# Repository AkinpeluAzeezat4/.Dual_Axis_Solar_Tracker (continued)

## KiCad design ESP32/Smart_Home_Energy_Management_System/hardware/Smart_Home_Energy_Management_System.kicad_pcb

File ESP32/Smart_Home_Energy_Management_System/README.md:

# Smart Home Energy Management System

## Overview

This project is a modular Smart Home Energy Management System built around the ESP32-WROOM-32 using a structured PlatformIO architecture.

The system monitors the real electrical load using a PZEM-004T v3.0 energy meter and automatically manages household loads between the inverter supply and PHCN/Grid supply based on:

- Actual measured load power
- User-configured inverter power rating
- User-configured load margin percentage
- User-configured power value for each load
- PHCN/Grid availability
- Inverter availability

The system is designed to reduce inverter overload by intelligently selecting which loads should remain on inverter and which loads should be moved to PHCN/Grid when needed.

The device includes:

- ST7920 128x64 graphical LCD display
- Rotary encoder setup menu
- PCA9555 I/O expander for relay and source sensing
- PZEM-004T v3.0 energy monitoring
- Automatic source management
- Local Wi-Fi web dashboard
- Breathing heartbeat LED
- Non-blocking firmware design

---

# Features

- ESP32-WROOM-32 based controller
- PZEM-004T v3.0 live energy monitoring
- Voltage, current, power, and energy display
- Six-load energy management
- Inverter and PHCN/Grid source decision logic
- PCA9555 GPIO expander support
- ST7920 128x64 LCD user interface
- Rotary encoder menu navigation
- First-boot setup mode
- Runtime setup access using long encoder press
- Local web dashboard through ESP32 Access Point mode
- Configurable relay load power values
- Configurable inverter power rating
- Configurable load margin percentage
- Preferences-based setting storage
- Non-blocking firmware architecture
- Modular PlatformIO project structure

---

# Hardware Used

## Main Controller

- ESP32-WROOM-32 development board

## Display

- ST7920 128x64 graphical LCD

## Energy Monitoring

- PZEM-004T v3.0 AC energy monitoring module

## GPIO Expansion

- PCA9555 16-bit I/O expander

## User Input

- Rotary encoder with push button

## Output Devices

- Six relay-controlled load channels
- Source switching relay channels
- Heartbeat LED
- Indicator output from PCA9555

## Power Source Monitoring

- PHCN/Grid sense input
- Inverter sense input

---

# Pin Configuration

## ESP32-WROOM-32 Pin Assignment

| Function | GPIO |
|---|---|
| Heartbeat LED | GPIO2 |
| ST7920 LCD CS | GPIO5 |
| ST7920 LCD SCLK | GPIO18 |
| ST7920 LCD MOSI | GPIO23 |
| PCA9555 SDA | GPIO21 |
| PCA9555 SCL | GPIO22 |
| PZEM RX to ESP32 | GPIO16 |
| PZEM TX from ESP32 | GPIO17 |
| Encoder A / CLK | GPIO26 |
| Encoder B / DT | GPIO25 |
| Encoder SW | GPIO27 |

---

# ST7920 LCD Connection

| LCD Function | ESP32 GPIO |
|---|---|
| CS / RS | GPIO5 |
| SCLK / E | GPIO18 |
| MOSI / RW | GPIO23 |

The ST7920 must be placed in serial/SPI mode.

---

# PZEM-004T v3.0 Connection

| PZEM Function | ESP32 GPIO |
|---|---|
| PZEM TX | GPIO16 |
| PZEM RX | GPIO17 |

The PZEM is used as the actual power sensor for the system. The firmware uses the measured PZEM power value for energy-management decisions.

---

# PCA9555 Configuration

Default PCA9555 I2C address:

```text
0x20
```

## PCA9555 Pin Assignment

| PCA9555 Pin | Function |
|---|---|
| P00 | Load 1 source relay |
| P01 | Load 1 load relay |
| P02 | Load 2 source relay |
| P03 | Load 2 load relay |
| P04 | Load 3 source relay |
| P05 | Load 3 load relay |
| P06 | Load 4 source relay |
| P07 | Load 4 load relay |
| P10 | Load 5 source relay |
| P11 | Load 5 load relay |
| P12 | Load 6 source relay |
| P13 | Load 6 load relay |
| P14 | Indicator output |
| P15 | PHCN/Grid sense input |
| P16 | Inverter sense input |
| P17 | 12V enable output |

---

# Source Sense Logic

The firmware reads PHCN/Grid and inverter availability from the PCA9555 input pins.

The active logic is controlled in `Pins.cpp`:

```cpp
const bool SOURCE_SENSE_ACTIVE_HIGH = true;
const bool INVERTER_SENSE_ACTIVE_HIGH = true;
```

If the source-sensing circuit gives LOW when the source is available, change the values to:

```cpp
const bool SOURCE_SENSE_ACTIVE_HIGH = false;
const bool INVERTER_SENSE_ACTIVE_HIGH = false;
```

---

# Load Management Logic

The system does not depend on fixed assumed load values for its running decision.

It uses:

- Actual live power from the PZEM sensor
- User-saved inverter power rating
- User-saved load margin percentage
- User-saved load power value for each relay channel
- Real PHCN/Grid availability input
- Real inverter availability input

## Effective Inverter Limit

The effective inverter limit is calculated using:

```text
Effective Limit = Inverter Power Rating x Load Margin Percentage
```

Example:

```text
Inverter Rating = 5000 W
Load Margin = 90 %
Effective Limit = 4500 W
```

## Relay Source Meaning

```text
INVERTER = Load remains powered from inverter
PHCN     = Load is moved to grid/PHCN
```

When the load is within a safe range, the system keeps loads on inverter.

When the measured load approaches or exceeds the safe inverter limit and PHCN/Grid is available, the system selects which loads should remain on inverter and moves other loads to PHCN/Grid to protect the inverter.

If the inverter is unavailable, the system moves the loads away from inverter.

---

# LCD Operation Guide

The LCD shows two main runtime screens:

## Load Status Screen

This screen shows the source status of each load channel.

```text
INV = Load is on inverter
GRD = Load is on PHCN/Grid
```

## Consumption Screen

This screen shows live PZEM readings:

- Voltage
- Current
- Power
- Energy

The device alternates between the load status screen and the consumption screen during normal operation.

---

# Encoder Operation Guide

## First Boot Setup

If the device has not been configured before, it automatically enters setup mode.

## Boot Setup Entry

During startup, hold the encoder button within the boot window to enter setup mode.

```text
Boot window: 5 seconds
Required hold time: 3 seconds
```

## Runtime Setup Entry

During normal operation, hold the encoder button to enter setup mode.

```text
Required hold time: 5 seconds
```

## Menu Navigation

| Action | Function |
|---|---|
| Rotate encoder | Move through menu / change value |
| Press encoder | Select item / move to next setting |
| Long press encoder | Enter setup mode from runtime |

---

# Setup Menu

The setup menu contains:

- Relay Mode
- Timer Setup
- WiFi Config
- System Setup
- Exit

## Relay Mode

Relay Mode is used to set the configured power rating for each load channel.

The six load channels are configured one after another:

```text
Relay 1 Load Power
Relay 2 Load Power
Relay 3 Load Power
Relay 4 Load Power
Relay 5 Load Power
Relay 6 Load Power
```

The configured load values are saved to ESP32 Preferences memory.

## System Setup

System Setup is used to set:

- Inverter Power Rating
- Load Margin Percentage

The inverter power rating should match the real inverter capacity.

The load margin percentage defines how much of the inverter rating should be used before the system starts protecting the inverter.

## WiFi Config

WiFi Config displays the local server information.

Default Access Point:

```text
SSID: SHEMS-Controller
Password: *****
IP Address: 192.168.4.1
```

The password is masked in this README for GitHub publishing. The actual value can be changed in the local server module.

---

# Local Web Dashboard

The ESP32 creates a local Wi-Fi Access Point.

Connect a phone or laptop to the device Wi-Fi network, then open:

```text
http://192.168.4.1
```

The dashboard displays:

- Voltage
- Current
- Actual load power
- Energy
- PHCN/Grid status
- Inverter status
- Effective inverter limit
- Load-management decision
- Relay source status
- Relay configured load power values

The dashboard also allows updating the inverter rating, load margin, and relay load power values.

---

# Default Configuration

| Parameter | Default Value |
|---|---:|
| Relay 1 Load Power | 500 W |
| Relay 2 Load Power | 700 W |
| Relay 3 Load Power | 900 W |
| Relay 4 Load Power | 1200 W |
| Relay 5 Load Power | 1500 W |
| Relay 6 Load Power | 2000 W |
| Inverter Power Rating | 5000 W |
| Load Margin | 90 % |

These values can be changed from the LCD setup menu or the local web dashboard.

---

# Project Structure

```text
lib/
├── Actuators/
│   ├── load_relay/
│   └── source_relay/
├── Control/
│   ├── error_handling/
│   └── sleep_wake/
├── Display/
│   ├── lcd_screen/
│   └── led_indicator/
├── Drivers/
│   └── gpio_expander/
├── Input/
│   └── rotary_encoder/
├── Pins/
├── Power/
│   ├── inverter_sense/
│   ├── nepa_sense/
│   └── regulator/
├── Sensors/
│   └── pzem_sensor/
├── System/
│   ├── config_manager/
│   ├── load_manager/
│   ├── local_server/
│   ├── ndelay/
│   ├── reset/
│   └── shared_var/

src/
└── main.cpp
```

---

# PlatformIO Environment

```ini
[platformio]
default_envs = esp32dev

[env:esp32dev]
platform = espressif32@6.5.0
board = esp32dev
framework = arduino
monitor_speed = 115200
lib_deps =
    olikraus/U8g2@^2.36.17
    mandulaj/PZEM-004T-v30@^1.2.1
build_flags =
    -DARDUINO_USB_CDC_ON_BOOT=0
```

---

# Build and Upload

## Build

```bash
pio run
```

## Upload

```bash
pio run --target upload
```

## Serial Monitor

```bash
pio device monitor
```

---

# Operation Flow

1. Power on the system.
2. The ESP32 initializes the LCD, encoder, PCA9555, relays, PZEM, local server, and saved configuration.
3. If the system has not been configured before, setup mode opens automatically.
4. Configure relay load power values and inverter settings.
5. During runtime, the PZEM measures actual voltage, current, power, and energy.
6. The source-sense inputs report PHCN/Grid and inverter availability.
7. The load manager checks the actual load against the inverter safe limit.
8. If the load is safe, loads remain on inverter.
9. If the inverter is close to overload and PHCN/Grid is available, selected loads are moved to PHCN/Grid.
10. The LCD and web dashboard show the current system state.

---

# Important Notes

- The PZEM must be wired correctly because the system uses it for live load decisions.
- Do not use assumed sensor values during final deployment.
- Configure the actual inverter rating before testing the load-management behavior.
- Configure each relay load power according to the real appliance connected to that load channel.
- Confirm the PHCN/Grid and inverter sense logic before connecting real loads.
- Use properly rated relays, contactors, and wiring for AC load switching.
- Use isolation and proper protection when working with mains voltage.
- The firmware is designed to be non-blocking and should not use `delay()` in the main control flow.

---

# Safety Warning

This project involves AC mains power and inverter/grid source switching. All high-voltage wiring should be handled carefully and tested with proper isolation, fusing, earthing, and protection devices.

For real installation, use correctly rated relays or contactors and ensure there is no unsafe back-feed between inverter and PHCN/Grid sources.

---

# Future Improvements

- Real-time graphing on the local dashboard
- Manual override from the web dashboard
- Load priority setup from LCD
- OTA update support
- Cloud logging
- MQTT integration
- Mobile app integration
- SD card logging
- Historical energy report

---

# Author

Egbe Raymond

Electrical / Electronic Engineer  
Embedded Systems Developer  
Full Stack Developer

---

# License

This project is intended for educational, prototype, and development purposes.

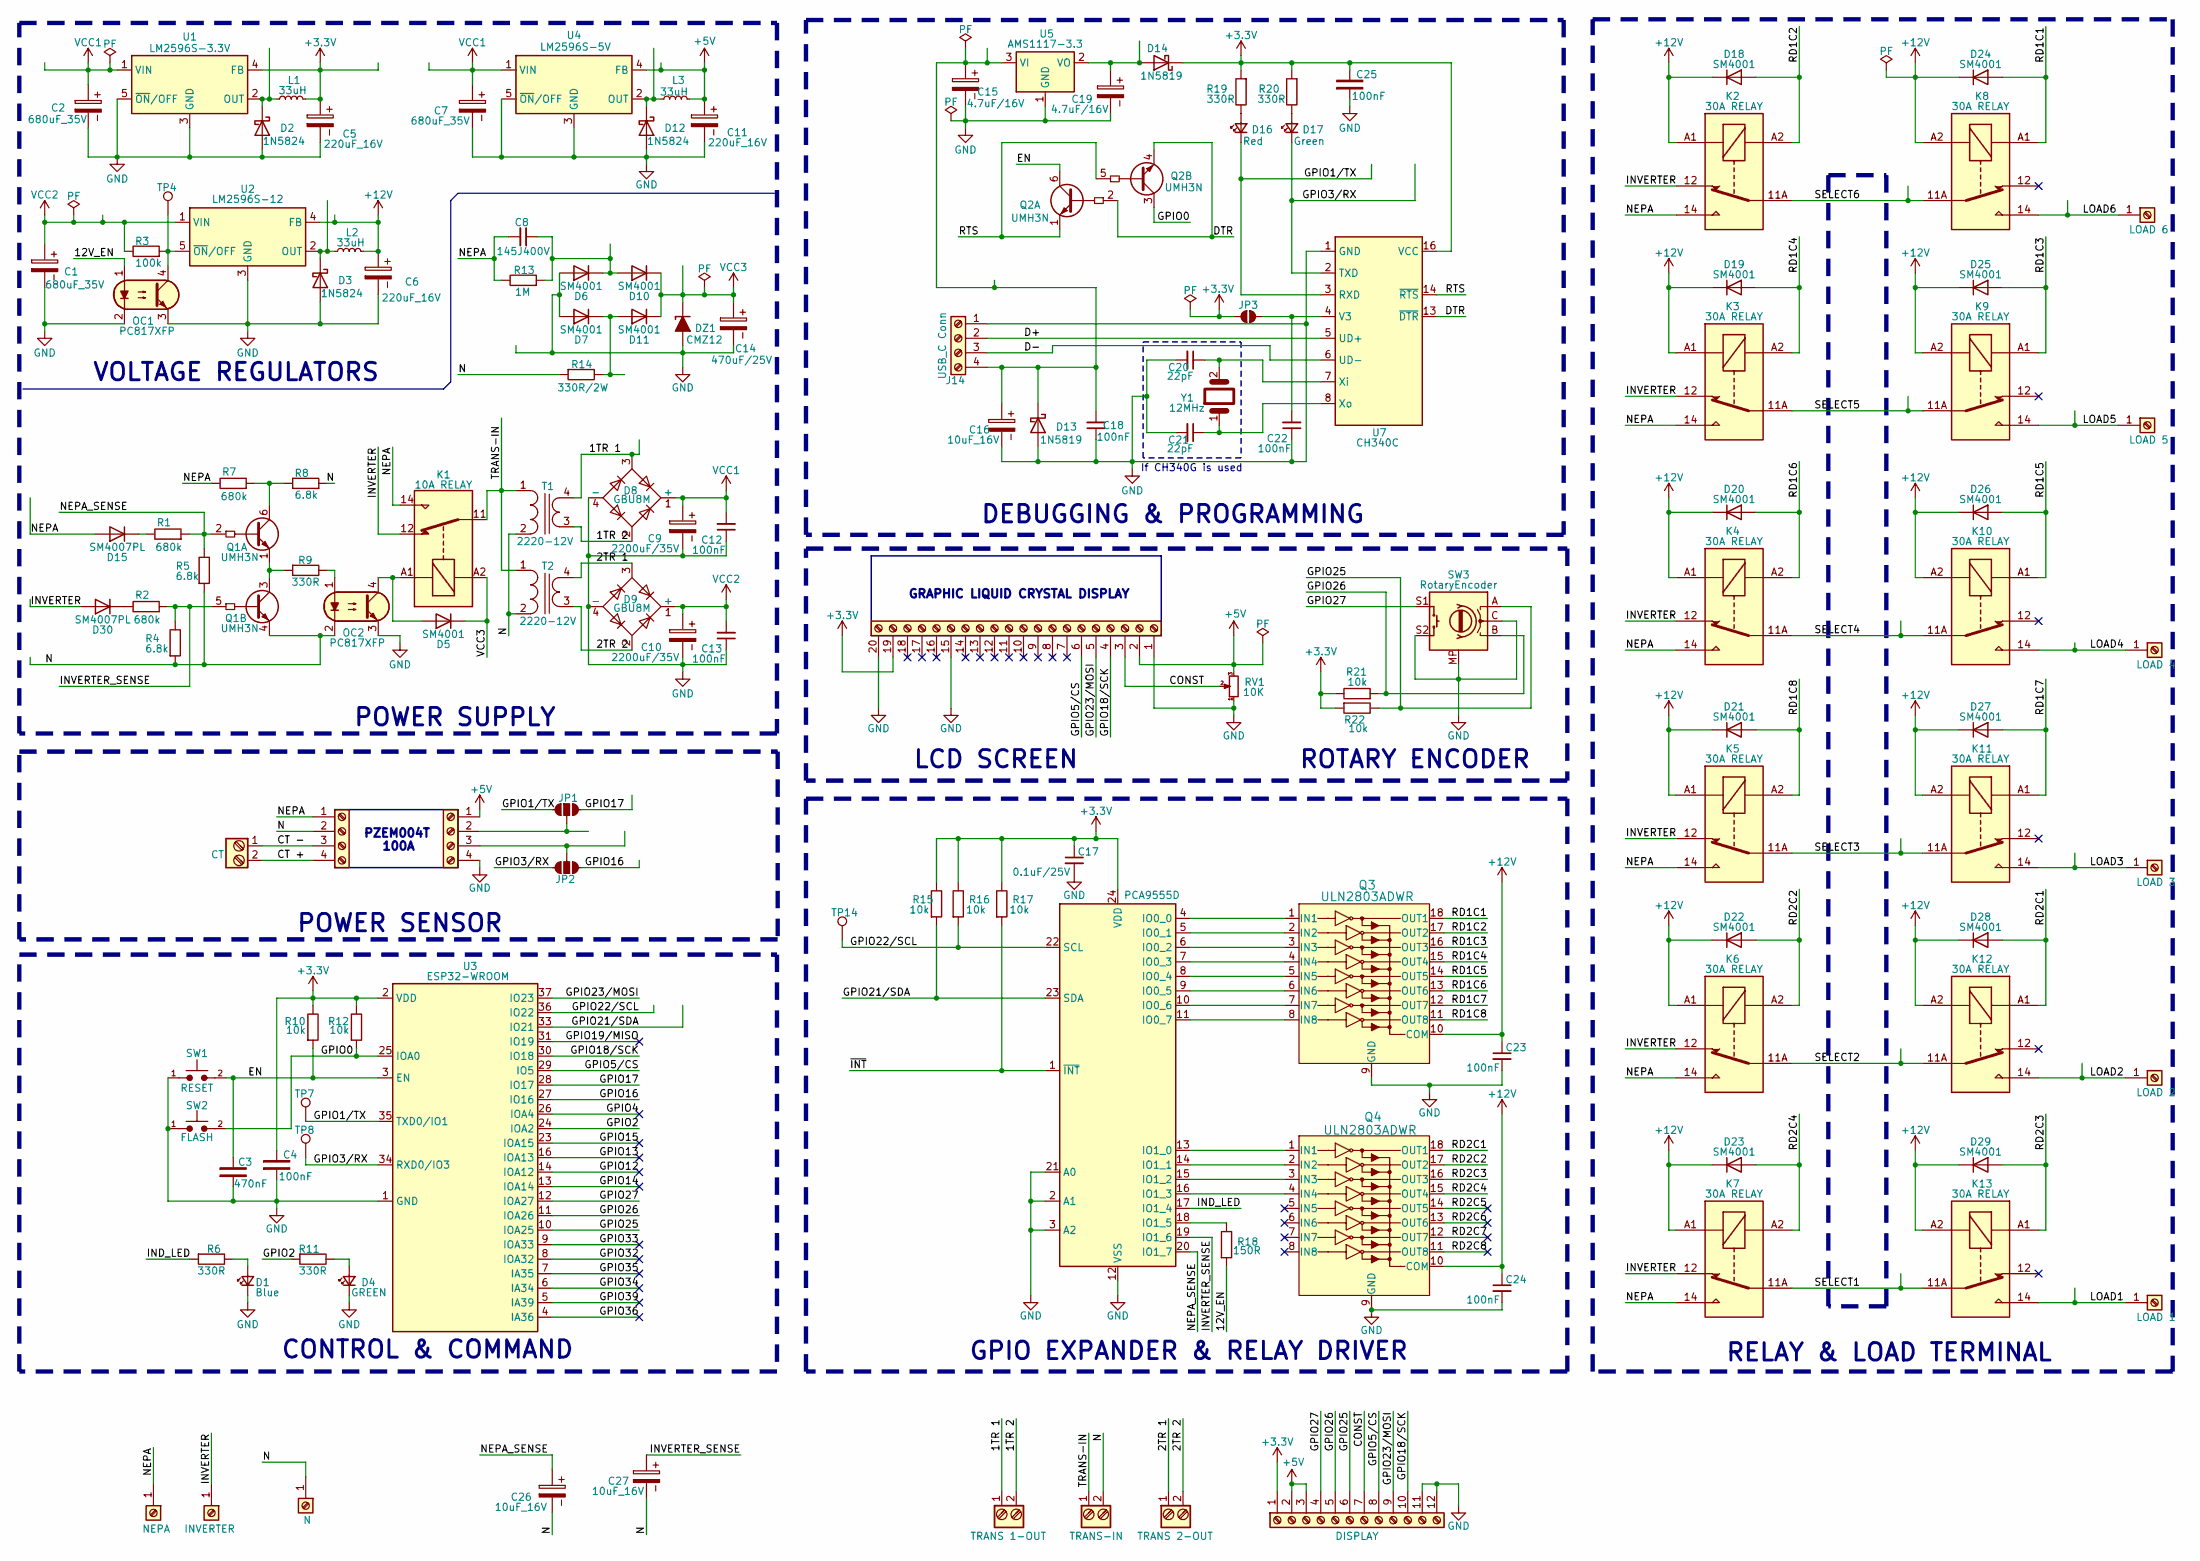
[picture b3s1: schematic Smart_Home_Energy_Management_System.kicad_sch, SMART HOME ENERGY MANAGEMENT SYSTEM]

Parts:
C1, C2, C7: 680uF_35V; CP_Elec_10x12.5
C3: 470nF; C_0805
C4, C12, C13, C18, C22, C25: 100nF; C_0805
C5, C6, C11: 220uF_16V; CP_Elec_6.3x7.7
C8: 145J400V; C_Rect_L19.0mm_W6.0mm_P15.00mm_MKS4
C9, C10: 2200uF/35V; CP_Radial_D18.0mm_P7.50mm
C14: 470uF/25V; CP_Elec_8x11.9
C15: 4.7uF/16V; C_CASE-B-3528-21(mm)
C16, C26, C27: 10uF_16V; C_CASE-B-3528-21(mm)
C17: 0.1uF/25V; C_0805; Voltage 25V; Tolerance 20%
C19: 4.7uF/16V; CP_EIA-3216-18_Kemet-A
C20, C21: 22pF; C_0805
C23, C24: 100nF; C_0805; Voltage 25V; Tolerance 20%
D1: Blue; LED_D3.0mm
D2, D3, D12: 1N5824; D_SMA
D4: GREEN; LED_D3.0mm
D5, D6, D7, D10, D11, D18, D19, D20, D21, D22, D23, D24, D25, D26, D27, D28, D29: SM4001; D_SMA
D8, D9: GBU8M; Diode_Bridge_Vishay_GBU
D13, D14: 1N5819; D_SMA
D15, D30: SM4007PL; D_SMA
D16: Red; LED_D3.0mm
D17: Green; LED_D3.0mm
DZ1: CMZ12; D_SOD-123
J1: NEPA; TestPoint_Plated_Hole_D5.0mm
J2: INVERTER; TestPoint_Plated_Hole_D5.0mm
J3: CT; PinHeader_1x02_P2.54mm_Vertical
J6: PZEM_LOAD; TerminalBlock_MaiXu_MX126-5.0-04P_1x04_P5.00mm
J10: N; TestPoint_Plated_Hole_D5.0mm
J11: PZEM_SIG; PinHeader_1x04_P2.54mm_Vertical
J14: USB_C Conn; PinHeader_1x04_P2.54mm_Vertical
J15: TRANS 1-OUT; TerminalBlock_Phoenix_PT-1,5-2-5.0-H_1x02_P5.00mm_Horizontal
J16: 128X64 GLCD
J17: TRANS-IN; TerminalBlock_Phoenix_PT-1,5-2-5.0-H_1x02_P5.00mm_Horizontal
J18: TRANS 2-OUT; TerminalBlock_Phoenix_PT-1,5-2-5.0-H_1x02_P5.00mm_Horizontal
J19: DISPLAY; PinHeader_1x12_P2.54mm_Vertical
J20: LOAD 6; TestPoint_Plated_Hole_D5.0mm
J21: LOAD 5; TestPoint_Plated_Hole_D5.0mm
J22: LOAD 4; TestPoint_Plated_Hole_D5.0mm
J23: LOAD 3; TestPoint_Plated_Hole_D5.0mm
J24: LOAD 2; TestPoint_Plated_Hole_D5.0mm
J25: LOAD 1; TestPoint_Plated_Hole_D5.0mm
JP1, JP2: SolderJumper-3_P1.3mm_Open_Pad1.0x1.5mm
JP3: SolderJumper-2_P1.3mm_Open_Pad1.0x1.5mm
K1: 10A RELAY; Relay_SPDT_Finder_36.11
K2, K3, K4, K5, K6, K7, K8, K9, K10, K11, K12, K13: 30A RELAY; Relay_SPDT_RAYEX-L90
L1, L2, L3: 33uH; L_12x12mm_H6mm
OC1, OC2: PC817XFP; SOP-4_4.4x2.6mm_P1.27mm
Q1, Q2: UMH3N; SOT-363_SC-70-6
Q3, Q4: ULN2803ADWR; SOIC-18_W7.5mm; MPN ULN2803ADWR; Digi-Key_PN 296-15777-1-ND
R1, R2, R7: 680k; R_0805
R3: 100k; R_0805
R4, R5, R8: 6.8k; R_0805
R6, R9, R11, R19, R20: 330R; R_0805
R10, R12, R15, R16, R17, R21, R22: 10k; R_0805
R13: 1M; R_Axial_DIN0207_L6.3mm_D2.5mm_P7.62mm_Horizontal
R14: 330R/2W; R_Axial_DIN0309_L9.0mm_D3.2mm_P20.32mm_Horizontal
R18: 150R; R_0805
RV1: 10K; Potentiometer_Bourns_3296W_Vertical
SW1: RESET; SW_TS-1088-AR02016
SW2: FLASH; SW_TS-1088-AR02016
SW3: RotaryEncoder
T1, T2: 2220-12V
TP4, TP7, TP8, TP14: TestPoint; TestPoint_Pad_D1.5mm
U1: LM2596S-3.3V; TO-263-5_L10.2-W8.9-P1.70-TL
U2: LM2596S-12; TO-263-5_L10.2-W8.9-P1.70-TL
U3: ESP32-WROOM; ESP32-WROOM-32E
U4: LM2596S-5V; TO-263-5_L10.2-W8.9-P1.70-TL
U5: AMS1117-3.3; SOT-223-3_L6.5-W3.4-P2.30-LS7.0-BR
U6: PCA9555D; SOIC-24W_7.5x15.4mm_P1.27mm
U7: CH340C; SOIC-16_3.9x9.9mm_P1.27mm
Y1: 12MHz; CRYSTAL-SMD_L11.5-W4.8-LS12.7

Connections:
+3.3V: C4.2, C5.1, C17.1, C25.2, D14.1 (K), J16.19, J19.1, JP3.2 (B), L1.2, R10.2, R12.2, R15.2, R16.2, R17.2, R19.1, R20.1, R21.2, R22.1, U1.4 (FB), U3.2 (VDD), U6.24 (VDD), U7.16 (VCC)
+5V: C11.1, J11.1, J16.2, J19.2, J19.3, L3.2, RV1.3, U4.4 (FB)
+12V: C6.1, C23.1, C24.1, D18.1 (K), D19.1 (K), D20.1 (K), D21.1 (K), D22.1 (K), D23.1 (K), D24.1 (K), D25.1 (K), D26.1 (K), D27.1 (K), D28.1 (K), D29.1 (K), K2.A1, K3.A1, K4.A1, K5.A1, K6.A1, K7.A1, K8.A2, K9.A2, K10.A2, K11.A2, K12.A2, K13.A2, L2.2, Q3.10 (COM), Q4.10 (COM), U2.4 (FB)
/1TR 1: D8.3, J15.1, T1.4 (SB)
/1TR 2: D8.2, J15.2, T1.3 (SA)
/2TR 1: D9.3, J18.1, T2.4 (SB)
/2TR 2: D9.2, J18.2, T2.3 (SA)
/12V_EN: OC1.1, R18.1
/CONST: J16.3, J19.7, RV1.2
/CT +: J3.2, J6.4
/CT -: J3.1, J6.3
/D+: J14.2, U7.5 (UD+)
/D-: J14.3, U7.6 (UD-)
/DTR: Q2.2 (B1), Q2.4 (E2), U7.13 (~DTR)
/EN: C3.2, Q2.6 (C1), R10.1, SW1.2, U3.3 (EN)
/GPIO0: Q2.3 (C2), R12.1, SW2.2, U3.25 (IOA0)
/GPIO1/TX: D16.1 (K), JP1.1 (A), TP7.1, U3.35 (TXD0/IO1), U7.3 (RXD)
/GPIO2: R11.1, U3.24 (IOA2)
/GPIO3/RX: D17.1 (K), JP2.3 (C), TP8.1, U3.34 (RXD0/IO3), U7.2 (TXD)
/GPIO4: U3.26 (IOA4)
/GPIO5/CS: J16.6, J19.8, U3.29 (IO5)
/GPIO12: U3.14 (IOA12)
/GPIO13: U3.16 (IOA13)
/GPIO14: U3.13 (IOA14)
/GPIO15: U3.23 (IOA15)
/GPIO16: JP2.1 (A), U3.27 (IO16)
/GPIO17: JP1.3 (C), U3.28 (IO17)
/GPIO18/SCK: J16.4, J19.10, U3.30 (IO18)
/GPIO19/MISO: U3.31 (IO19)
/GPIO21/SDA: R15.1, U3.33 (IO21), U6.23 (SDA)
/GPIO22/SCL: R16.1, TP14.1, U3.36 (IO22), U6.22 (SCL)
/GPIO23/MOSI: J16.5, J19.9, U3.37 (IO23)
/GPIO25: J19.6, R22.2, SW3.A, U3.10 (IOA25)
/GPIO26: J19.5, R21.1, SW3.B, U3.11 (IOA26)
/GPIO27: J19.4, SW3.S1, U3.12 (IOA27)
/GPIO32: U3.8 (IOA32)
/GPIO33: U3.9 (IOA33)
/GPIO34: U3.6 (IA34)
/GPIO35: U3.7 (IA35)
/GPIO36: U3.4 (IA36)
/GPIO39: U3.5 (IA39)
/IND_LED: R6.1, U6.17 (IO1_4)
/INVERTER: D30.2 (A), J2.1, K1.12, K2.12, K3.12, K4.12, K5.12, K6.12, K7.12
/INVERTER_SENSE: C27.1, Q1.5 (B2), R2.1, R4.2, U6.19 (IO1_6)
/LOAD1: J25.1, K13.14
/LOAD2: J24.1, K12.14
/LOAD3: J23.1, K11.14
/LOAD4: J22.1, K10.14
/LOAD5: J21.1, K9.14
/LOAD6: J20.1, K8.14
/N: C26.2, C27.2, J6.2, J10.1, J17.2, OC2.2, Q1.4 (E2), R4.1, R5.1, R8.1, R14.1, T1.2 (AB), T2.2 (AB)
/NEPA: C8.2, D15.2 (A), J1.1, J6.1, K1.14, K2.14, K3.14, K4.14, K5.14, K6.14, K7.14, R7.2, R13.2
/NEPA_SENSE: C26.1, Q1.2 (B1), R1.1, R5.2, U6.20 (IO1_7)
/RD1C1: D24.2 (A), K8.A1, Q3.18 (OUT1)
/RD1C2: D18.2 (A), K2.A2, Q3.17 (OUT2)
/RD1C3: D25.2 (A), K9.A1, Q3.16 (OUT3)
/RD1C4: D19.2 (A), K3.A2, Q3.15 (OUT4)
/RD1C5: D26.2 (A), K10.A1, Q3.14 (OUT5)
/RD1C6: D20.2 (A), K4.A2, Q3.13 (OUT6)
/RD1C7: D27.2 (A), K11.A1, Q3.12 (OUT7)
/RD1C8: D21.2 (A), K5.A2, Q3.11 (OUT8)
/RD2C1: D28.2 (A), K12.A1, Q4.18 (OUT1)
/RD2C2: D22.2 (A), K6.A2, Q4.17 (OUT2)
/RD2C3: D29.2 (A), K13.A1, Q4.16 (OUT3)
/RD2C4: D23.2 (A), K7.A2, Q4.15 (OUT4)
/RD2C5: Q4.14 (OUT5)
/RD2C6: Q4.13 (OUT6)
/RD2C7: Q4.12 (OUT7)
/RD2C8: Q4.11 (OUT8)
/RTS: Q2.1 (E1), Q2.5 (B2), U7.14 (~RTS)
/SELECT1: K7.11A, K7.11B, K13.11A, K13.11B
/SELECT2: K6.11A, K6.11B, K12.11A, K12.11B
/SELECT3: K5.11A, K5.11B, K11.11A, K11.11B
/SELECT4: K4.11A, K4.11B, K10.11A, K10.11B
/SELECT5: K3.11A, K3.11B, K9.11A, K9.11B
/SELECT6: K2.11A, K2.11B, K8.11A, K8.11B
/TRANS-IN: J17.1, K1.11, T1.1 (AA), T2.1 (AA)
/~INT: R17.1, U6.1 (~INT)
GND: C1.2, C2.2, C3.1, C4.1, C5.2, C6.2, C7.2, C9.2, C10.2, C11.2, C12.1, C13.1, C14.2, C15.2, C16.2, C17.2, C18.1, C19.2, C20.2, C21.2, C22.1, C23.2, C24.2, C25.1, D1.1 (K), D2.2 (A), D3.2 (A), D4.1 (K), D6.2 (A), D7.2 (A), D8.4 (-), D9.4 (-), D12.2 (A), D13.2 (A), DZ1.2 (A), J11.4, J14.1, J16.1, J16.15, J16.20, J19.11, J19.12, OC1.2, OC1.3, OC2.3, Q3.9 (GND), Q4.9 (GND), RV1.1, SW1.1, SW2.1, SW3.C, SW3.MP, SW3.S2, U1.3 (GND), U1.5 (~ON/OFF), U1.6 (GND), U2.3 (GND), U2.6 (GND), U3.1 (GND), U3.15 (GND), U3.38 (GND), U3.39 (GND), U4.3 (GND), U4.5 (~ON/OFF), U4.6 (GND), U5.1 (GND), U6.2 (A1), U6.3 (A2), U6.12 (VSS), U6.21 (A0), U7.1 (GND)
unnamed: D1.2 (A), R6.2
unnamed: D2.1 (K), L1.1, U1.2 (OUT)
unnamed: D3.1 (K), L2.1, U2.2 (OUT)
unnamed: D4.2 (A), R11.2
unnamed: D5.2 (A), K1.A1, OC2.4
unnamed: C8.1, D6.1 (K), D10.2 (A), R13.1
unnamed: D7.1 (K), D11.2 (A), R14.2
unnamed: D12.1 (K), L3.1, U4.2 (OUT)
unnamed: C15.1, C16.1, C18.2, D13.1 (K), J14.4, U5.3 (VI)
unnamed: C19.1, D14.2 (A), U5.2 (VO), U5.4 (VO)
unnamed: D15.1 (K), R1.2
unnamed: D16.2 (A), R19.2
unnamed: D17.2 (A), R20.2
unnamed: D30.1 (K), R2.2
unnamed: J11.2, JP1.2 (B)
unnamed: J11.3, JP2.2 (B)
unnamed: C22.2, JP3.1 (A), U7.4 (V3)
unnamed: OC2.1, R9.2
unnamed: Q1.6 (C1), R7.1, R8.2
unnamed: Q1.1 (E1), Q1.3 (C2), R9.1
unnamed: Q3.1 (IN1), U6.4 (IO0_0)
unnamed: Q3.2 (IN2), U6.5 (IO0_1)
unnamed: Q3.3 (IN3), U6.6 (IO0_2)
unnamed: Q3.4 (IN4), U6.7 (IO0_3)
unnamed: Q3.5 (IN5), U6.8 (IO0_4)
unnamed: Q3.6 (IN6), U6.9 (IO0_5)
unnamed: Q3.7 (IN7), U6.10 (IO0_6)
unnamed: Q3.8 (IN8), U6.11 (IO0_7)
unnamed: Q4.1 (IN1), U6.13 (IO1_0)
unnamed: Q4.2 (IN2), U6.14 (IO1_1)
unnamed: Q4.3 (IN3), U6.15 (IO1_2)
unnamed: Q4.4 (IN4), U6.16 (IO1_3)
unnamed: OC1.4, R3.1, TP4.1, U2.5 (~ON/OFF)
unnamed: R18.2, U6.18 (IO1_5)
unnamed: C20.1, U7.7 (Xi), Y1.2
unnamed: C21.1, U7.8 (Xo), Y1.1
VCC1: C2.1, C7.1, C9.1, C12.2, D8.1 (+), U1.1 (VIN), U4.1 (VIN)
VCC2: C1.1, C10.1, C13.2, D9.1 (+), R3.2, U2.1 (VIN)
VCC3: C14.1, D5.1 (K), D10.1 (K), D11.1 (K), DZ1.1 (K), K1.A2

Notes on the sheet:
VOLTAGE REGULATORS
LCD SCREEN
ROTARY ENCODER
POWER SUPPLY
If CH340G is used
DEBUGGING & PROGRAMMING
POWER SENSOR
RELAY & LOAD TERMINAL
CONTROL & COMMAND
PZEM004T
GRAPHIC LIQUID CRYSTAL DISPLAY
100A
GPIO EXPANDER & RELAY DRIVER

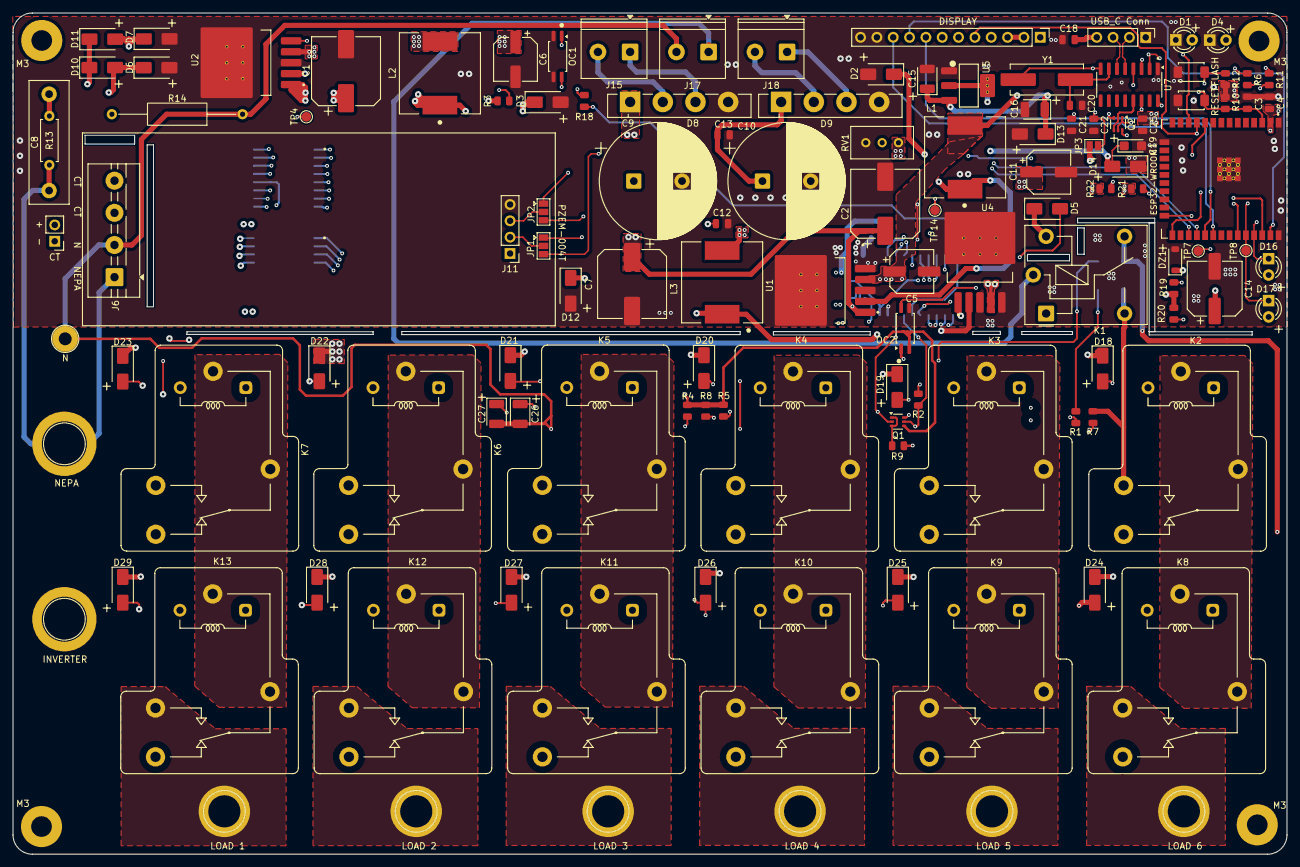
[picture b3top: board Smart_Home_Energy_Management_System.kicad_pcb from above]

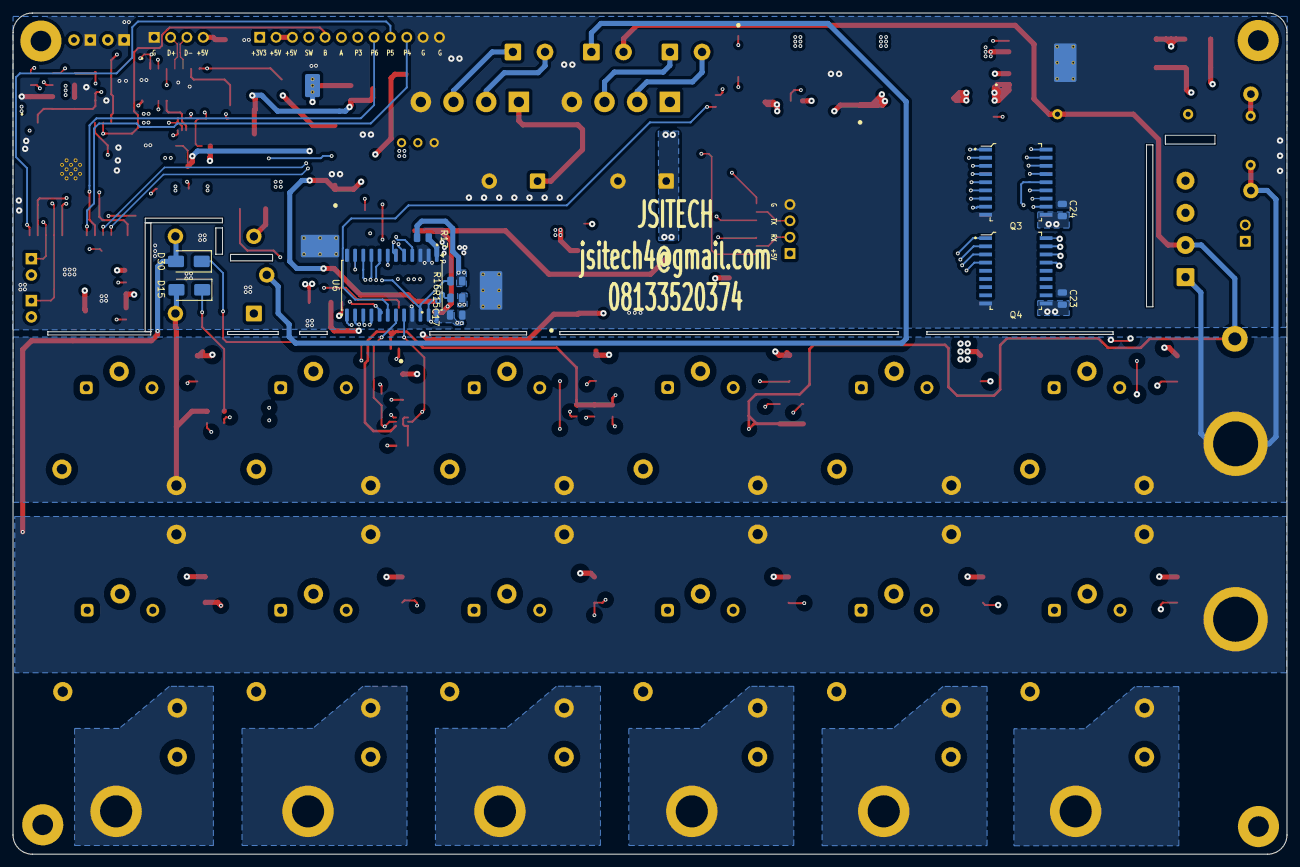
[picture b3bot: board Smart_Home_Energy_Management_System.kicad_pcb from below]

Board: 4 copper layers, 198.1 x 130.8 mm, 137 parts (11 on the bottom side), 102 nets.

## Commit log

2026-02-03 sync updates
2026-02-05 Updated document with Real PCB Images
2026-02-05 restore files
2026-02-05 Files rearrangement
2026-02-13 updates from home
2026-03-26 🚀 Initial KiCad structure setup
2026-04-17 99% code for mesh system
2026-04-17 Change on ledPin lib
2026-04-17 Change on indicator lib
2026-04-17 Change in ledPin lib
2026-04-17 Change in ledPin lib
    Changed the parameter type of the 'begin' function from 'int' to 'uint8_t' for better type safety.
2026-04-17 Change in buzzer lib
2026-04-17 Change in buzzer lib
    Added functions to start and stop alarm, and check alarm status.
2026-04-17 Change in ledPin lib
    Implement LED indicator functionality with PWM control and pause feature.
2026-04-17 Change in ledPin lib
    Enhance LED indicator functionality with PWM and pause logic.
2026-04-17 Change in battery level lib
    Refactor battery level functions to accept dynamic pin and scale parameters, improving flexibility and readability.
2026-04-17 Change in battery level lib
    Updated the begin function to accept parameters for pin and scale, and renamed voltage and percentage functions for clarity.
2026-04-17 Change in battery level lib
    Updated battery level functions to include pin and scale parameters.
2026-04-17 Change in battery level lib
    Refactor battery level management to allow dynamic pin and scale factor configuration. Update reading logic to include timing control.
2026-04-17 Change in battery level lib
2026-04-17 Change in battery level lib
    Updated battery level functions to accept pin and scale parameters.
2026-04-17 Change in battery level lib
    Refactor battery level management to allow dynamic pin and scale factor configuration.
2026-04-17 Change in battery level lib
    Refactor battery level functions to include pin and scale parameters.
2026-04-17 Change in battery level lib
    Updated battery level header to include pin parameter and default scale value.
2026-04-17 update from work
2026-04-24 updated projects
2026-04-28 updated from work
2026-04-29 update from home
2026-04-30 change in the pin assignment
2026-05-02 Update projects
2026-05-08 Updated README FILE
    Expanded the README to provide detailed project information, including features, system concept, authentication flow, web page functions, hardware used, and future improvements.
2026-05-08 Updated README file
    Added detailed project overview, features, hardware specifications, pin configuration, operation guide, and future improvements for the Dual Axis Solar Tracker.
2026-05-08 Updated README file
    This README provides an overview of the Motion Detection and Alarm Mesh System project, detailing its architecture, features, hardware used, pin configuration, and operating instructions.
2026-05-08 Updated README file
    Expanded the README.md to provide detailed project overview, features, system architecture, hardware used, pin configuration, operating guide, and future improvements.
2026-05-08 Updated README file
    Added comprehensive documentation for the Predictive Maintenance System, detailing features, hardware used, pin configuration, logging, LED behavior, relay protection, project structure, build instru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
2026-05-08 Updated README file
    Expanded the README with detailed project overview, features, hardware used, pin configuration, connection guides, setup instructions, operation flow, safety warnings, and future improvements.
2026-05-08 Updated README file
    Updated project description, features, hardware used, pin configuration, and operation flow in the README.
2026-05-08 Updated README file
    Added detailed project overview, features, hardware used, pin configuration, and operation instructions to the README.
2026-05-08 Updated README file
    Updated project title and description for clarity.
2026-05-08 Updated README file
    Added detailed project overview, features, hardware used, pin configuration, PlatformIO environment, author information, and license details.
2026-05-08 Updated README file
    Updated README.md to provide detailed project information, features, hardware used, pin configuration, logging, LED behavior, relay protection, project structure, PlatformIO environment, build and up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
2026-05-08 Updated README file
    Expanded the README to include project overview, features, controller details, pin assignments, I2C devices, LCD interface, relay outputs, local web dashboard, operation instructions, firmware struct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
2026-05-08 Updated README file
    Updated project description and features for the Solar Powered Smart Irrigation System. Added detailed sections on hardware used, pin configuration, system operation, and troubleshooting.
2026-05-08 Updated README file
    Updated README.md to provide detailed project overview, features, hardware used, pin configuration, system operation, and safety guidelines for the Smart Robotic Car with PID control.
2026-05-08 Updated README file
    Expanded the README to provide detailed project overview, features, hardware used, system operation, zone setup, main intrusion logic, event logic, email alert behavior, and troubleshooting steps.
2026-05-08 Updated README file
    Updated README to provide detailed project overview, features, hardware used, pin configuration, system operation, and troubleshooting steps for the Water Level Monitoring and Automatic Pump Control 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
2026-05-31 Updated project files
